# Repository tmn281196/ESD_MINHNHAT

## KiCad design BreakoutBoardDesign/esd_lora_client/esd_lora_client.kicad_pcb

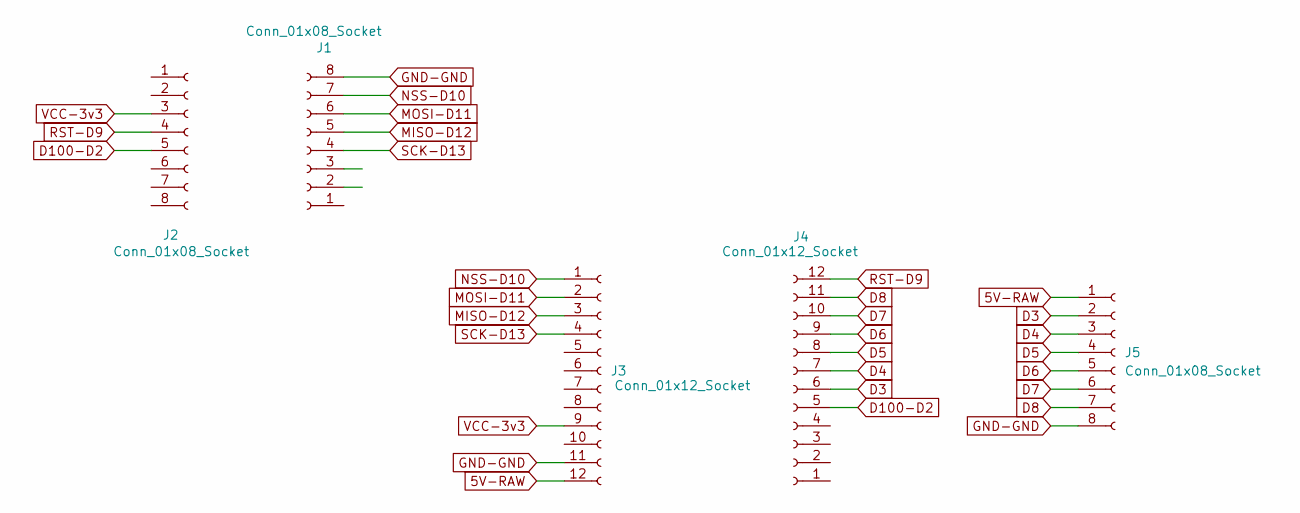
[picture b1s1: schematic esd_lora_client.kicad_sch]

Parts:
J1, J2, J5: Conn_01x08_Socket; PinSocket_1x08_P2.54mm_Vertical
J3, J4: Conn_01x12_Socket; PinSocket_1x12_P2.54mm_Vertical

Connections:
5V-RAW: J3.12, J5.1
D3: J4.6, J5.2
D4: J4.7, J5.3
D5: J4.8, J5.4
D6: J4.9, J5.5
D7: J4.10, J5.6
D8: J4.11, J5.7
D100-D2: J2.5, J4.5
GND-GND: J1.8, J3.11, J5.8
MISO-D12: J1.5, J3.3
MOSI-D11: J1.6, J3.2
NSS-D10: J1.7, J3.1
RST-D9: J2.4, J4.12
SCK-D13: J1.4, J3.4
VCC-3v3: J2.3, J3.9

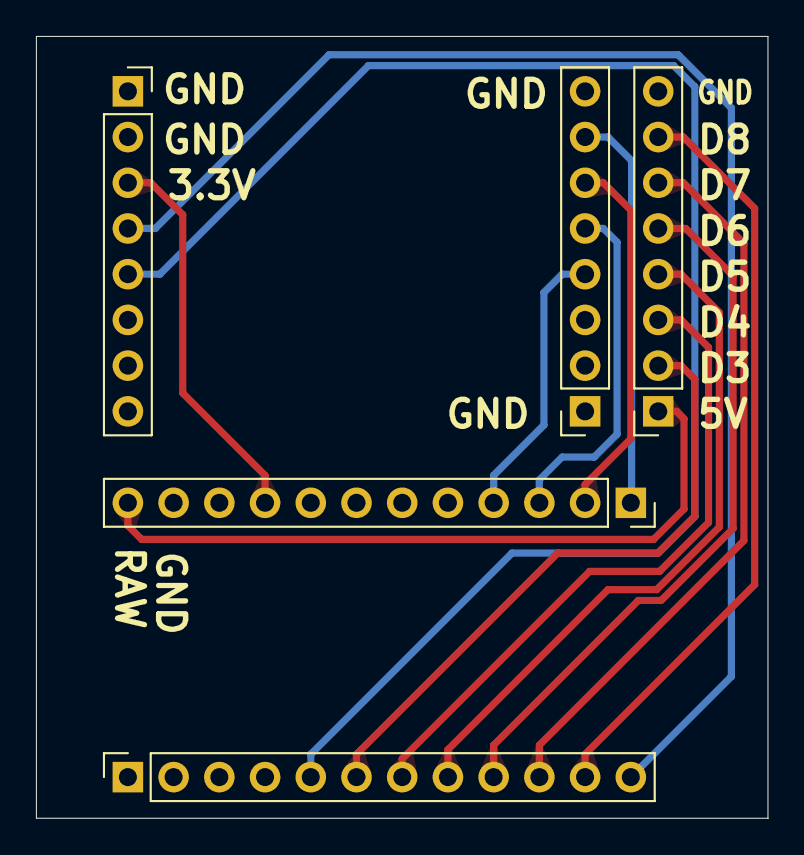
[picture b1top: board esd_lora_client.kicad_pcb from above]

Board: 2 copper layers, 40.6 x 43.4 mm, 5 parts (0 on the bottom side), 15 nets.
